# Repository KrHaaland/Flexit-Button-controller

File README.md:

# Flexit-Button-controller

ESP32-C5 button panel for the **Flexit Tradition-S** ventilation unit. Replaces or parallels the original 5-button control panel with an isolated emulator that adds **Wi-Fi (2.4 GHz + 5 GHz)** and **MQTT** for smart-home integration.

The ESP32-C5 is currently one of the few cheap ESP modules with dual-band Wi-Fi 6, which lets the panel live on either band depending on your home network and signal coverage.

## What it does

The board exposes 5 channels, each mirroring one button + indicator LED on the original Flexit Tradition-S panel:

- **5 button outputs** drive AQY212S solid-state opto-couplers in parallel with on-board tactile switches. A short pulse on a channel looks electrically identical to a finger press, in galvanic isolation from the Flexit unit.
- **5 LED inputs** read the indicator-LED state back from the panel net.

You get three ways to interact with the panel:

1. The physical tactile buttons on the PCB (works without firmware).
2. A self-served web UI (Wi-Fi setup, manual trigger, live LED dots, pulse tuning, MQTT setup).
3. MQTT — subscribe to LED state changes, publish to fire buttons.

## Hardware

- **Module:** ESP32-C5-Mini (USB-C, dual-band Wi-Fi 6, 4 MB flash, no PSRAM)
- **Isolation:** 5x AQY212S solid-state relays (LED-driven MOSFET output, ~3 ms switching)
- **Connector to Flexit:** Micro-MaTch 2x6 (J1), carrying 5 button signals + 5 LED signals + 5 V supply + GND, mating with the cable on the back of the original Flexit panel.
- **PCB:** KiCad files under [`PCB/`](PCB/) (Gerbers/BOM/positions for the fab in [`PCB/production/`](PCB/production/)).

### Pin mapping (set in `FW/ESP32-C5-Flexit/src/main.cpp`)

| Channel | Trigger out | LED in |
|--------:|:-----------:|:------:|
| 1       | IO4         | IO5    |
| 2       | IO3         | IO6    |
| 3       | IO2         | IO7    |
| 4       | IO1         | IO8    |
| 5       | IO0         | IO9    |

Trigger outputs idle LOW and pulse HIGH for ~300 ms (configurable from the UI) to emulate a press. LED inputs are read with `INPUT_PULLDOWN`; the Flexit drives them HIGH when an indicator is lit.

## Build & flash

Requires [PlatformIO](https://platformio.org/) (`pip install platformio` or the VSCode extension).

```bash
cd FW/ESP32-C5-Flexit
pio run                       # compile
pio run -t upload             # flash via USB-C
pio device monitor -b 115200  # serial log
```

The C5 enumerates as `/dev/ttyACM*` (built-in USB Serial JTAG, no driver needed).

## First-time setup

1. Power the ESP32-C5 over USB-C, or via the J1 connector once mounted.
2. With no saved Wi-Fi, the board comes up as an access point:
   - SSID: `Flexit-Setup`
   - Password: `fibonacci` (default; the Wi-Fi form lets you set a custom one if you don't want the documented value).
3. Join that AP and open <http://192.168.4.1/> (also reachable as `http://flexit.local/` via mDNS).
4. In the **Wi-Fi** section, enter your home SSID + password and click *Save & reboot*. You can optionally set a custom AP fallback password in the same form — it persists in NVS. The board joins your network and is then reachable on its STA IP or via `flexit.local`.

Wi-Fi credentials and the AP-password override are stored in NVS and survive a reflash. *Forget & reboot to AP* wipes the Wi-Fi creds but keeps the AP password override.

If the home network is briefly unreachable at boot, the board lands in AP mode but periodically retries (every 5 min) so a transient router outage doesn't strand it.

## Web interface

| Section            | What it does |
|--------------------|--------------|
| **Knapper**        | 5 trigger buttons + 5 live LED indicators (polled every 400 ms). |
| **Pulse duration** | Length of the simulated button press (20–2000 ms, default 300 ms). Useful if a Flexit function requires a long-press. |
| **MQTT**           | Broker host/port, optional user/password, base topic, heartbeat republish interval, live connection status, MAC-derived client ID. |
| **Wi-Fi**          | SSID + password, *Save & reboot* into STA, *Forget* clears creds. Banner at top shows current STA/AP state, RSSI, IP. |

Everything except Wi-Fi changes applies live without reboot.

## MQTT

When the board is in STA mode (joined to your Wi-Fi) and a broker host is configured, it connects to the broker and stays connected with auto-reconnect and a Last Will. With base topic `flexit` (default — configurable in the UI):

| Topic                      | Direction | Payload                  | Notes |
|----------------------------|-----------|--------------------------|-------|
| `flexit/led/1..5/state`    | publish   | `ON` / `OFF`             | Retained. Sent on every transition; also republished periodically if heartbeat > 0. |
| `flexit/sw/1..5/trigger`   | subscribe | any (optional `<ms>`)    | Any payload triggers a pulse on that channel. A numeric payload overrides the configured pulse duration for that single trigger. |
| `flexit/status`            | publish   | `online` / `offline`     | LWT, retained. |

Client ID is `flexit-<MAC>` (12 hex chars from the chip's eFuse MAC) — globally unique per ESP32. Use it in your broker's ACL.

### Home Assistant example

```yaml
mqtt:
  binary_sensor:
    - name: "Flexit LED 1"
      state_topic: "flexit/led/1/state"
      payload_on: "ON"
      payload_off: "OFF"
    # ... repeat for 2..5
  button:
    - name: "Flexit button 1"
      command_topic: "flexit/sw/1/trigger"
    # ... repeat for 2..5
```

## Firmware updates (OTA)

Once the device is on your Wi-Fi (STA mode), you don't need USB again — there are two ways to push a new build:

### Web upload

1. Build locally: `cd FW/ESP32-C5-Flexit && pio run`. The artifact is `.pio/build/esp32-c5-devkitc1-n4/firmware.bin`.
2. Open the device's web UI (`http://flexit.local/` or its STA IP).
3. Scroll to the **Firmware** section. The current version, build timestamp and free slot space are shown.
4. Pick the new `firmware.bin`, click **Upload & reboot**. The progress bar tracks the upload, then the board reboots into the new image. The page auto-reloads after ~8 s.

### PlatformIO push

```bash
cd FW/ESP32-C5-Flexit
pio run -e esp32-c5-devkitc1-n4-ota -t upload
```

This uses the espota protocol over mDNS at `flexit.local:3232`.

### Partition layout

Switched from the Arduino default (`default.csv`, 1.25 MB per app slot) to `min_spiffs.csv` (1.875 MB per slot, two slots, plus 128 KB SPIFFS). NVS stays at offset `0x9000` so saved Wi-Fi / MQTT / pulse settings survive the migration when you flash the OTA-enabled image for the first time.

### Robustness

The HTTP OTA path is hardened against the common failure modes:

- The 5 button-trigger pins are forced LOW at the start of every upload, and `/trigger` + MQTT-fired triggers are ignored during the upload — a press in flight can't keep the opto-coupler latched through the multi-second multipart parse.
- Idle timeout (10 s) and total timeout (120 s) abort slow-loris uploads.
- A sticky abort flag short-circuits the rest of the upload as soon as `Update.begin`, a short write, or `Update.end` reports an error — no point in streaming 1 MB just to fail at the end.
- MQTT publishes `offline` retained to `<base>/status` and disconnects gracefully before the reboot, so subscribers see the flap immediately instead of waiting out the 30 s keepalive.
- Wi-Fi disconnect + `server.close()` + an 800 ms settle before `ESP.restart()` give the TCP FIN and the HTTP 200 response enough time to flush on a marginal link.
- A Wi-Fi event handler re-binds mDNS and ArduinoOTA whenever the STA interface gets a new IP, so wireless reflash keeps working after a router reboot or AP roam.

### Security model

There's **no authentication** on either OTA path or on the other config endpoints. The assumption is that your Wi-Fi LAN is trusted (this is a home device behind your router, not on the open internet). Anyone with route to the device on TCP 80 or 3232 can re-flash it.

The AP fallback PSK is `fibonacci` by default — yes, the same one this README mentions, on purpose. The Wi-Fi form lets you override it per device if you'd rather not advertise it in the source. Override is persisted in NVS.

If you need stricter controls (HTTP Basic auth on `/update`, an ArduinoOTA password, signed firmware images, broker ACLs, VLANs), open an issue.

## Repo layout

```
.
├── FW/ESP32-C5-Flexit/      PlatformIO project (Arduino framework)
│   ├── src/main.cpp         Firmware
│   └── src/index_html.h     Embedded web UI (single page)
├── PCB/                     KiCad schematic + PCB design
│   └── production/          Gerbers, BOM, positions for fab
└── knappepanel_flexit.kicad_pro
```

## Notes & quirks

- The board has 5 on-board tactile switches in parallel with the opto outputs, and 5 indicator LEDs on the LED nets, so it doubles as a stand-alone bench panel.
- ESP32-C5 boot prints `MSPI Timing: Failed to allocate dummy cacheline for PSRAM memory barrier!` — harmless, the C5-Mini has no PSRAM but the SDK looks for it.
- Verified against a Flexit Tradition-S. Other Flexit models with a different button matrix or LED drive scheme may need pin or polarity changes (see `LED_ACTIVE_HIGH` in `src/main.cpp`).

## License

No license set yet — treat as "all rights reserved" until one is added. Open an issue if you'd like a specific one (MIT / Apache-2.0 / CC-BY-SA for the hardware, etc.).

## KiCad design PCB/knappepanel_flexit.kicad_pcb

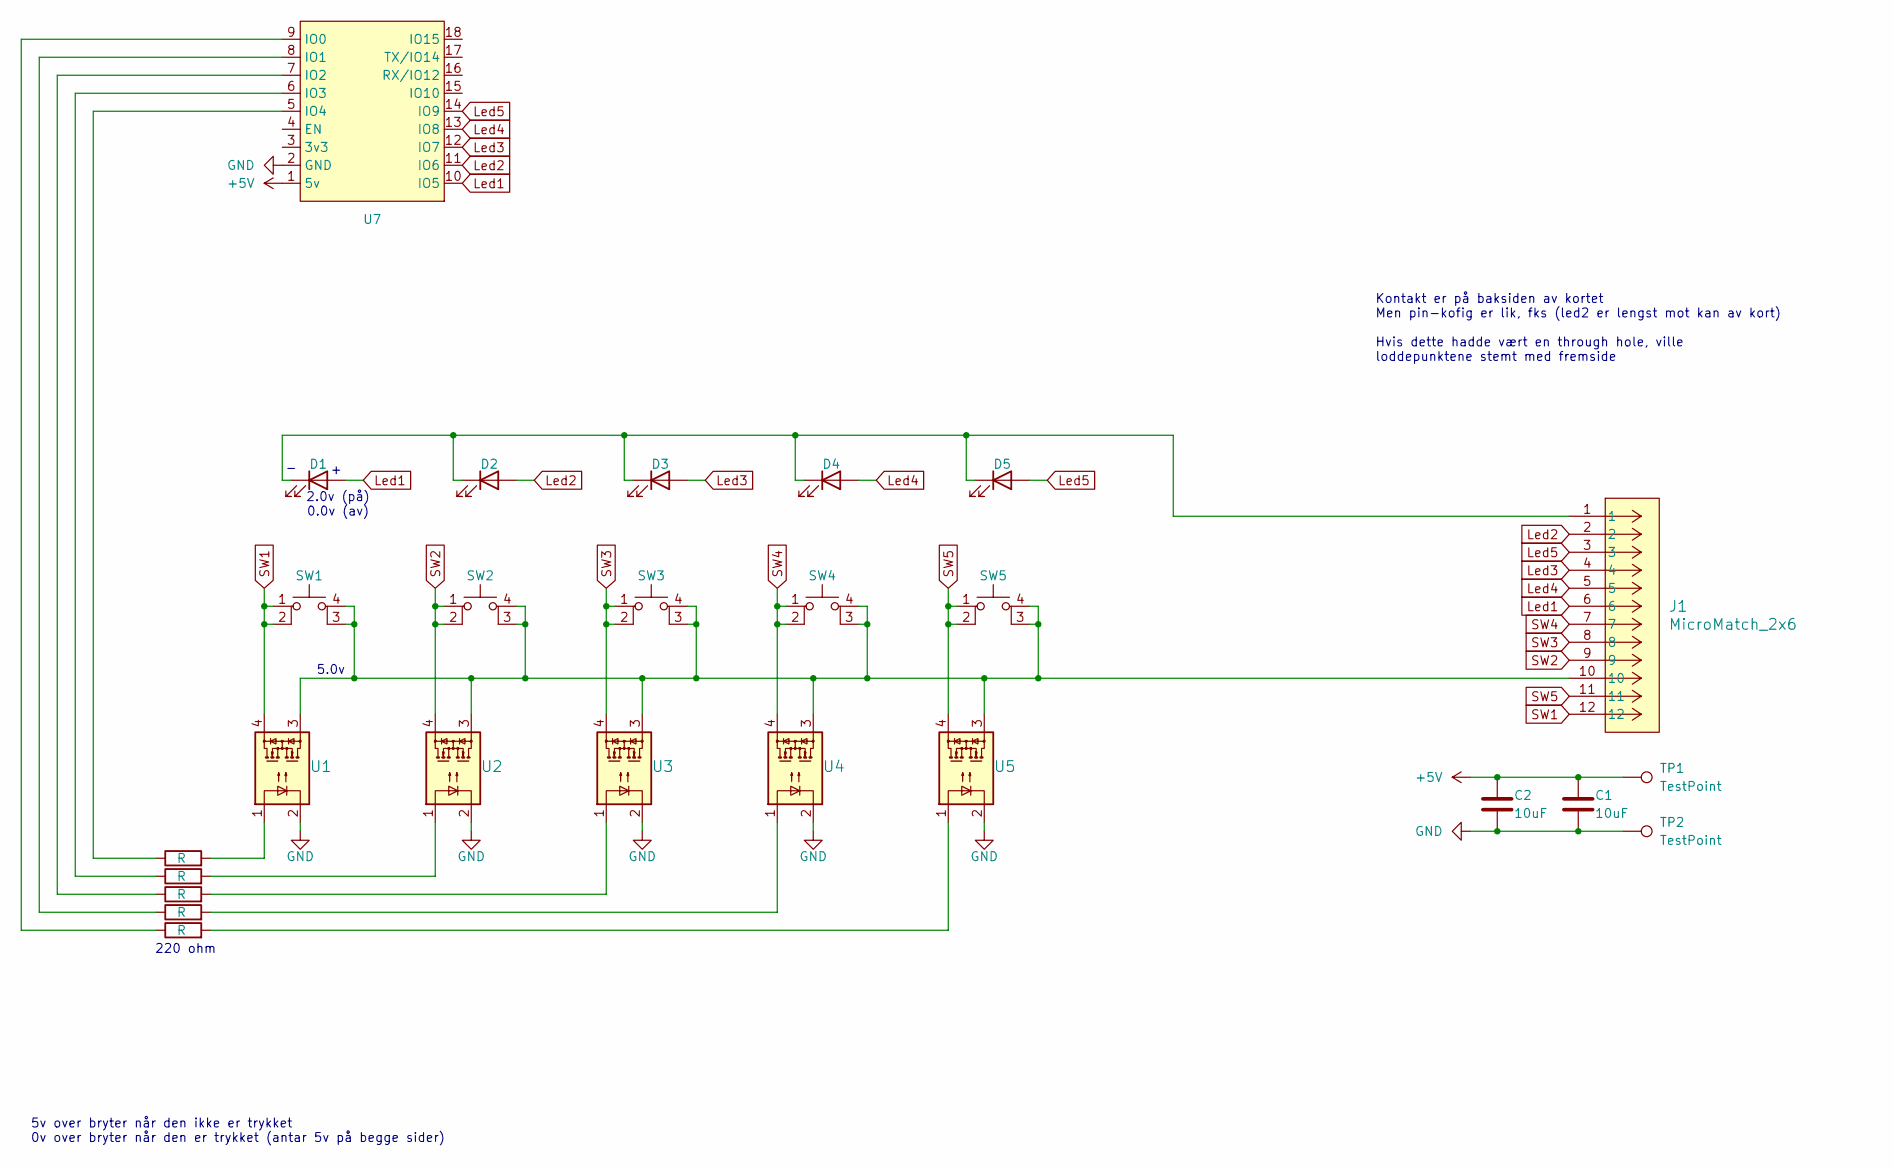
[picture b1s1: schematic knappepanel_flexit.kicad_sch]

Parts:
C1, C2: 10uF; C_0805_2012Metric
D1, D2, D3, D4, D5: LED; LED_1206_3216Metric
J1: MicroMatch_2x6; Micromatch_2x6
R1, R2, R3, R4, R5: R; R_0805_2012Metric
SW1, SW2, SW3, SW4, SW5: Tactile SW 6x6mm; LCSC Part C5127964
TP1, TP2: TestPoint; TestPoint_Pad_1.5x1.5mm
U1, U2, U3, U4, U5: AQY212S
U7: ESP32-C5Mini

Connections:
+5V: C1.1, C2.1, TP1.1 (1_1), U7.1 (5v)
GND: C1.2, C2.2, TP2.1 (1_1), U1.2, U2.2, U3.2, U4.2, U5.2, U7.2 (GND)
Led1: D1.2 (A), J1.6, U7.10 (IO5)
Led2: D2.2 (A), J1.2, U7.11 (IO6)
Led3: D3.2 (A), J1.4, U7.12 (IO7)
Led4: D4.2 (A), J1.5, U7.13 (IO8)
Led5: D5.2 (A), J1.3, U7.14 (IO9)
unnamed: D1.1 (K), D2.1 (K), D3.1 (K), D4.1 (K), D5.1 (K), J1.1
unnamed: J1.10, SW1.3, SW1.4, SW2.3, SW2.4, SW3.3, SW3.4, SW4.3, SW4.4, SW5.3, SW5.4, U1.3, U2.3, U3.3, U4.3, U5.3
unnamed: R1.2, U1.1
unnamed: R2.2, U2.1
unnamed: R3.2, U3.1
unnamed: R4.2, U4.1
unnamed: R5.2, U5.1
unnamed: R5.1, U7.9 (IO0)
unnamed: R4.1, U7.8 (IO1)
unnamed: R3.1, U7.7 (IO2)
unnamed: R2.1, U7.6 (IO3)
unnamed: R1.1, U7.5 (IO4)
SW1: J1.12, SW1.1, SW1.2, U1.4
SW2: J1.9, SW2.1, SW2.2, U2.4
SW3: J1.8, SW3.1, SW3.2, U3.4
SW4: J1.7, SW4.1, SW4.2, U4.4
SW5: J1.11, SW5.1, SW5.2, U5.4

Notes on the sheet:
5v over bryter når den ikke er trykket 0v over bryter når den er trykket (antar 5v på begge sider)
5.0v
2.0v (på) 0.0v (av)
Kontakt er på baksiden av kortet Men pin-kofig er lik, fks (led2 er lengst mot kan av kort) Hvis dette hadde vært en through hole, ville loddepunktene stemt med fremside
220 ohm

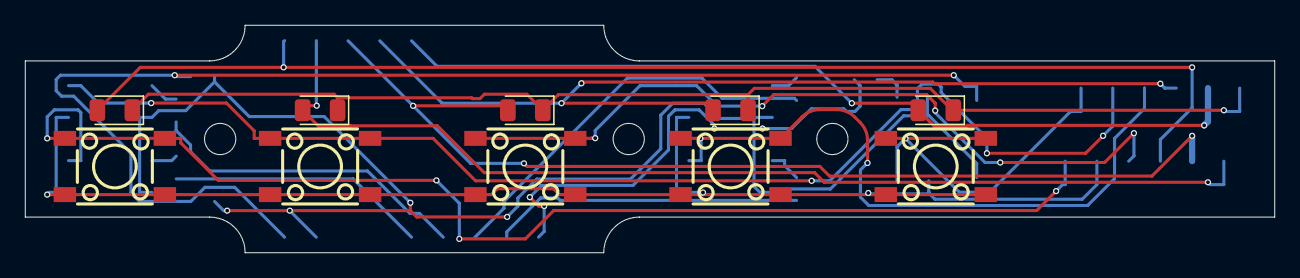
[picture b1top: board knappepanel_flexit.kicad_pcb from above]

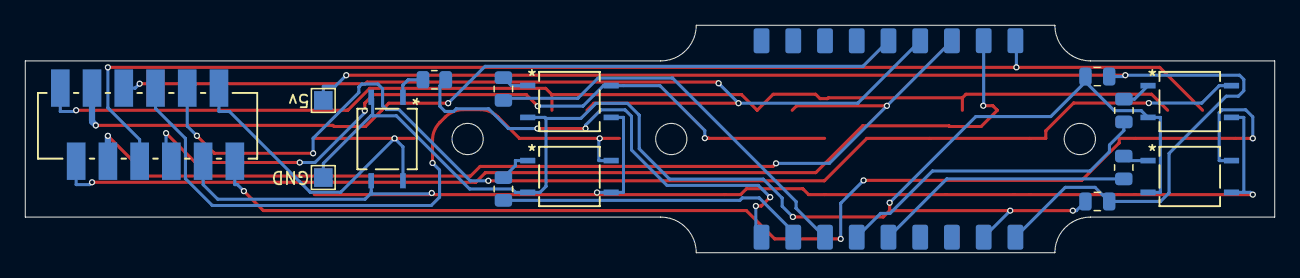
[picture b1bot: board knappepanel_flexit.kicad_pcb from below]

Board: 2 copper layers, 100.0 x 18.2 mm, 26 parts (16 on the bottom side), 24 nets.

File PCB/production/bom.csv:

Designator,Footprint,Quantity,Value,LCSC Part #
"C1, C2",0805,2,10uF,
"D1, D2, D3, D4, D5",1206,5,LED,
J1,Micromatch_2x6,1,MicroMatch_2x6,
"R1, R2, R3, R4, R5",0805,5,R,
"SW1, SW2, SW3, SW4, SW5",Tactile SW 6x6mm,5,Tactile SW 6x6mm,C5127964
"TP1, TP2",TestPoint_Pad_1.5x1.5mm,2,TestPoint,
"U1, U2, U3, U4, U5",AQY212S,5,AQY212S,
U7,ESP32-C5Mini,1,~,
